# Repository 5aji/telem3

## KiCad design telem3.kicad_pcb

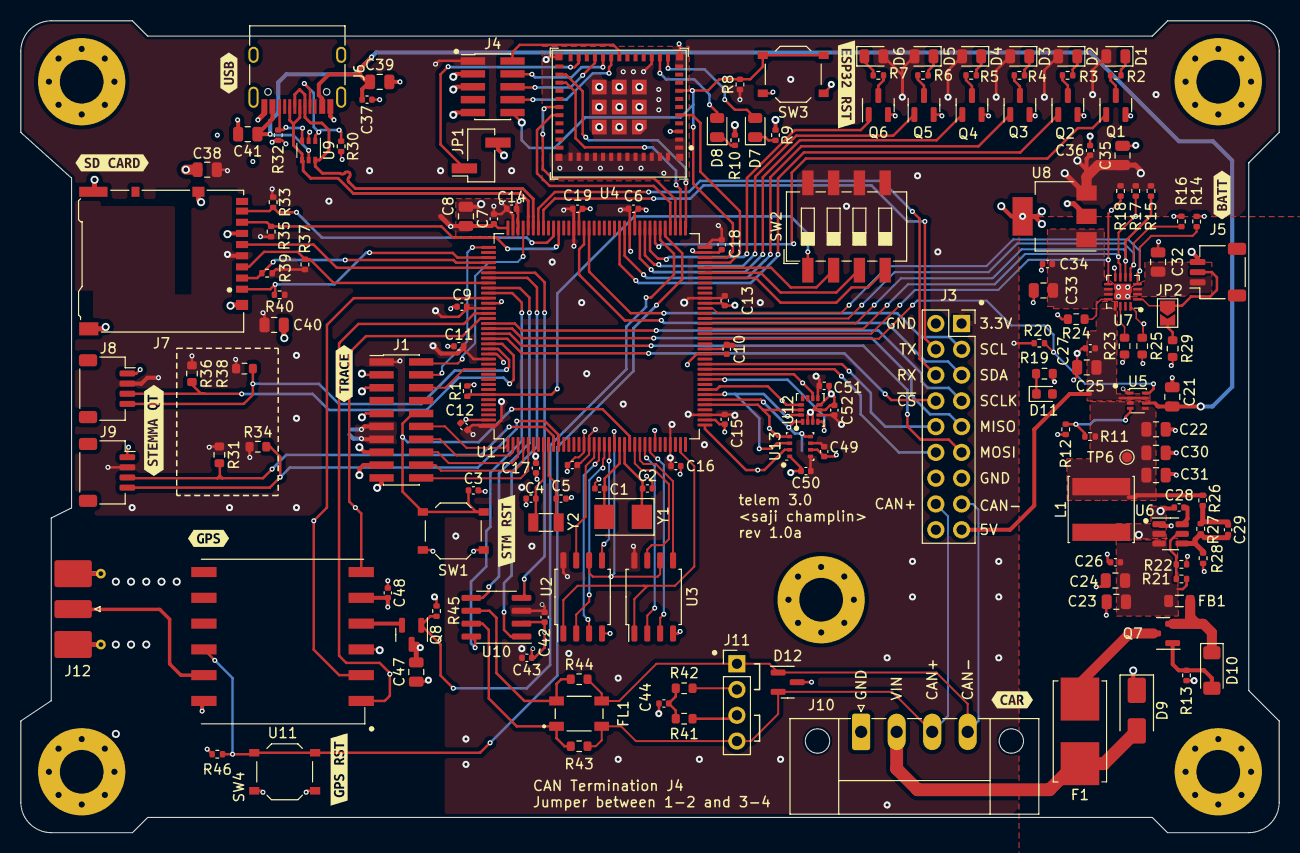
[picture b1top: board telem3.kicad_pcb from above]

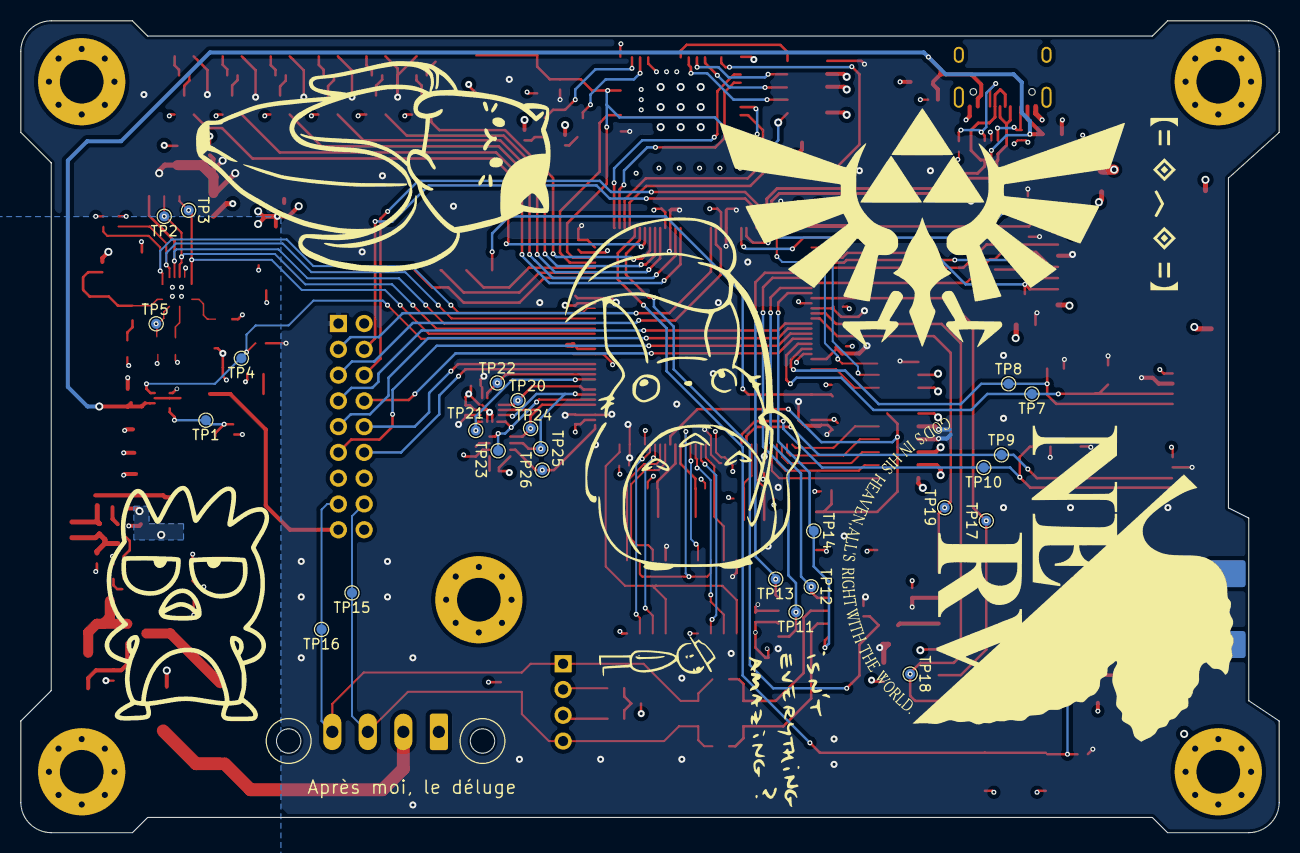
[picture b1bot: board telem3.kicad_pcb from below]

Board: 4 copper layers, 124.0 x 80.0 mm, 188 parts (25 on the bottom side), 139 nets.

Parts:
C1, C2: 20p; C_0402_1005Metric
C3, C9, C10, C11, C12, C13, C14, C15, C16, C17, C18, C19, C20, C26, C28, C34, C36, C37, C42, C43, C48, C49, C50, C51, C52: 0.1u; C_0402_1005Metric
C4, C5: 10p; C_0402_1005Metric
C6, C7, C27: 1u; C_0402_1005Metric
C8, C21, C22, C25, C32, C33, C35, C47: 4.7u; C_0805_2012Metric
C23, C24, C39, C41: 10u; C_0805_2012Metric
C29: 75p; C_0402_1005Metric
C30, C31, C38, C40: 22u; C_0805_2012Metric
C44: 4.7n; C_0402_1005Metric
D1: STA0; LED_0805_2012Metric
D2: STA1; LED_0805_2012Metric
D3: GOOD_LED; LED_0805_2012Metric
D4: STA2; LED_0805_2012Metric
D5: FAULT_LED; LED_0805_2012Metric
D6: STA3; LED_0805_2012Metric
D7: ESP_LED0; LED_0805_2012Metric
D8: ESP_LED1; LED_0805_2012Metric
D9: SMAJ30CA; D_SMA
D10: BZV55B10; D_MiniMELF
D11: 5V; LED_0603_1608Metric
D12: NUP2105L; SOT-23
F1: 2.5A; Fuseholder_Littelfuse_Nano2_154x
FB1: 600 @ 600MHz; L_0805_2012Metric
FL1: DLW43SH510XK2L; FIL_DLW43SH510XK2L
J1: STM32_TRACE; PinHeader_2x10_P1.27mm_Vertical_SMD
J3: EXPANSION_1; PinSocket_2x09_P2.54mm_Vertical
J4: ESP32_JTAG; PinHeader_2x05_P1.27mm_Vertical_SMD
J5: BAT; JST_SH_SM03B-SRSS-TB_1x03-1MP_P1.00mm_Horizontal
J6: STM_USBC; USB_C_Receptacle_HRO_TYPE-C-31-M-12
J7: Micro_SD_Card; microSD_HC_Hirose_DM3AT-SF-PEJM5
J8: QT1; JST_SH_SM04B-SRSS-TB_1x04-1MP_P1.00mm_Horizontal
J9: QT2; JST_SH_SM04B-SRSS-TB_1x04-1MP_P1.00mm_Horizontal
J10: Conn_01x04_Socket; PhoenixContact_MC_1,5_4-GF-3.5_1x04_P3.50mm_Horizontal_Thre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
J11: CAN_TERMINATION; PinHeader_1x04_P2.54mm_Vertical
J12: GPS_ANT; SMA_Molex_73251-2120_EdgeMount_Horizontal
JP1: ESP32_BOOTSEL; PinHeader_1x02_P2.54mm_Vertical_SMD_Pin1Right
JP2: BAT_TS_BYP; SolderJumper-2_P1.3mm_Open_TrianglePad1.0x1.5mm
L1: 15u; L_Changjiang_FNR6020S
Q1, Q2, Q3, Q4, Q5, Q6, Q8: 2N7002; SOT-23
Q7: IRLML9301; SOT-23
R1, R8, R11, R12, R13, R14, R15, R16, R17, R18, R20, R27, R33, R35, R37, R39, R40, R45, R46: 100k; R_0402_1005Metric
R2, R3, R4, R5, R6, R7, R9, R10: 330; R_0402_1005Metric
R19: 330; R_0603_1608Metric
R21: 511k; R_0402_1005Metric
R22: 105k; R_0402_1005Metric
R23: 46.4k; R_0603_1608Metric
R24: 1.18k; R_0603_1608Metric
R25: 1.13k; R_0603_1608Metric
R26: 49.9; R_0402_1005Metric
R28: 13.3k; R_0402_1005Metric
R29, R31, R34, R36, R38: 10k; R_0603_1608Metric
R30, R32: 5.1k; R_0402_1005Metric
R41, R42: 60R; R_0603_1608Metric
R43, R44: 0R; R_0603_1608Metric
SW1: RESET; SW_Push_1P1T_XKB_TS-1187A
SW2: OPT; SW_DIP_SPSTx04_Slide_6.7x11.72mm_W8.61mm_P2.54mm_LowProfile
SW3: ESP32_RST; SW_Push_1P1T_XKB_TS-1187A
SW4: GPS_RST; SW_Push_1P1T_XKB_TS-1187A
TP1: PR1; TestPoint_Pad_D1.0mm
TP2: ~{PGOOD}; TestPoint_Pad_D1.0mm
TP3: ~{CHG}; TestPoint_Pad_D1.0mm
TP4: ST; TestPoint_Pad_D1.0mm
TP5: BAT_CUR; TestPoint_Pad_D1.0mm
TP6: SW_5V; TestPoint_Pad_D1.0mm
TP7: QT1_SDA; TestPoint_Pad_D1.0mm
TP8: QT1_SCL; TestPoint_Pad_D1.0mm
TP9: QT2_SDA; TestPoint_Pad_D1.0mm
TP10: QT2_SCL; TestPoint_Pad_D1.0mm
TP11: CAN_TX; TestPoint_Pad_D1.0mm
TP12: CAN_SHDN; TestPoint_Pad_D1.0mm
TP13: CAN_RX; TestPoint_Pad_D1.0mm
TP14: CAN_STB; TestPoint_Pad_D1.0mm
TP15: CANH; TestPoint_Pad_D1.0mm
TP16: CANL; TestPoint_Pad_D1.0mm
TP17: GPS.TX; TestPoint_Pad_D1.0mm
TP18: GPS.RX; TestPoint_Pad_D1.0mm
TP19: 1PPS; TestPoint_Pad_D1.0mm
TP20: IMU_~{CS}; TestPoint_Pad_D1.0mm
TP21: IMU_INT_{1}; TestPoint_Pad_D1.0mm
TP22: IMU_INT_{2}; TestPoint_Pad_D1.0mm
TP23: SENSE_MISO; TestPoint_Pad_D1.0mm
TP24: SENSE_SCLK; TestPoint_Pad_D1.0mm
TP25: SENSE_MOSI; TestPoint_Pad_D1.0mm
TP26: BME_~{CS}; TestPoint_Pad_D1.0mm
U1: STM32L562ZETx; LQFP-144_20x20mm_P0.5mm
U2, U3: W25Q128JVS; SOIC-8_5.23x5.23mm_P1.27mm
U4: ESP32-C3-MINI-1; ESP32-C3-MINI-1U
U5: TPS2116; SOT-583-8
U6: TPS54202DDC; SOT-23-6
U7: BQ24075RGT; VQFN-16-1EP_3x3mm_P0.5mm_EP1.6x1.6mm
U8: AP7361C-33E; SOT-223-3_TabPin2
U9: NUP4202; SOT-363_SC-70-6
U10: TCAN334G; SOIC-8_3.9x4.9mm_P1.27mm
U11: L80-R; Quectel_L80-R
U12: LSM6DS3; LGA-14_3x2.5mm_P0.5mm_LayoutBorder3x4y
U13: BME280; Bosch_LGA-8_2.5x2.5mm_P0.65mm_ClockwisePinNumbering
Y1: 8MHz; Crystal_SMD_5032-2Pin_5.0x3.2mm
Y2: 32.768kHz; Crystal_SMD_3215-2Pin_3.2x1.5mm
kibuzzard-64E6B9AE: G***; kibuzzard-64E6B9AE
kibuzzard-64E6B9B9: G***; kibuzzard-64E6B9B9
kibuzzard-64E6B9C4: G***; kibuzzard-64E6B9C4
kibuzzard-64E6B9D9: G***; kibuzzard-64E6B9D9
kibuzzard-64E84E3F: G***; kibuzzard-64E84E3F
kibuzzard-64E84E26: G***; kibuzzard-64E84E26
kibuzzard-64EA17F0: G***; kibuzzard-64EA17F0
kibuzzard-64EA1880: G***; kibuzzard-64EA1880
kibuzzard-64ED289C: G***; kibuzzard-64ED289C
kibuzzard-64ED2075: G***; kibuzzard-64ED2075

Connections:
+3V3: C6.2, C7.2, C8.2, C9.2, C10.2, C11.2, C12.2, C13.2, C14.2, C15.2, C16.2, C17.2, C18.2, C19.2, C20.2, C35.1, C36.1, C38.1, C40.1, C42.1, C43.1, C47.2, C48.2, C49.1, C50.1, C51.1, C52.1, D1.2 (A), D2.2 (A), D3.2 (A), D4.2 (A), D5.2 (A), D6.2 (A), J1.1 (VTref), J1.11 (VTpwr), J1.13 (VTpwr), J3.1, J4.1 (VTref), J7.4 (VDD), J8.2, J9.2, Q8.3 (D), R8.1, R15.2, R17.2, R18.1, R20.1, R31.1, R33.1, R34.1, R35.1, R36.1, R37.1, R38.1, R39.1, R40.1, R45.1, R46.1, SW2.5, SW2.6, SW2.7, SW2.8, U1.6 (VBAT), U1.17 (VDD), U1.33 (VDDA), U1.39 (VDD), U1.52 (VDD), U1.62 (VDD), U1.72 (VDD), U1.84 (VDD), U1.95 (VDDIO2), U1.106 (VDDUSB), U1.108 (VDD), U1.121 (VDD), U1.131 (VDDIO2), U1.144 (VDD), U2.8 (VCC), U3.8 (VCC), U4.3 (3V3), U8.3 (VO), U10.3 (VCC), U11.5 (V_BCKP), U12.5 (VDDIO), U12.8 (VDD), U13.6 (VDDIO), U13.8 (VDD)
+5V: C25.1, C27.1, D11.2 (A), J3.17, U5.2 (VOUT), U5.7 (VOUT), U7.13 (IN)
/Board IO/CAN.RX: TP13.1, U1.114 (PD0), U10.4 (RXD)
/Board IO/CAN.SHDN: TP12.1, U1.117 (PD3), U10.5 (SHDN)
/Board IO/CAN.STB: TP14.1, U1.118 (PD4), U10.8 (STB)
/Board IO/CAN.TX: TP11.1, U1.115 (PD1), U10.1 (TXD)
/Board IO/QT1.SCL: J8.4, R38.2, TP8.1, U1.129 (PG14)
/Board IO/QT1.SDA: J8.3, R36.2, TP7.1, U1.128 (PG13)
/Board IO/QT2.SCL: J9.4, R34.2, TP10.1, U1.11 (PF1)
/Board IO/QT2.SDA: J9.3, R31.2, TP9.1, U1.10 (PF0)
/Board IO/SD.CLK: J7.5 (CLK), U1.113 (PC12)
/Board IO/SD.CMD: J7.3 (CMD), R37.2, U1.116 (PD2)
/Board IO/SD.DAT0: J7.7 (DAT0), R35.2, U1.98 (PC8)
/Board IO/SD.DAT1: J7.8 (DAT1), R33.2, U1.99 (PC9)
/Board IO/SD.DAT2: J7.1 (DAT2), R40.2, U1.111 (PC10)
/Board IO/SD.DAT3: J7.2 (DAT3/CD), R39.2, U1.112 (PC11)
/Board IO/USB_CC1: J6.A5 (CC1), R30.1, U9.1
/Board IO/USB_CC2: J6.B5 (CC2), R32.1, U9.3
/Board IO/USB_D+: J6.A6 (D+), J6.B6 (D+), U1.104 (PA12), U9.4
/Board IO/USB_D-: J6.A7 (D-), J6.B7 (D-), U1.103 (PA11), U9.6
/ESP32 Coprocessor/ESP32.CS: U1.73 (PB12), U4.26 (GPIO18/USB_D-)
/ESP32 Coprocessor/ESP32.EN: J4.10 (~RESET), R8.2, SW3.2, U1.70 (PB11), U4.8 (EN/CHIP_PU)
/ESP32 Coprocessor/ESP32.HNDSHK: U1.69 (PB10), U4.5 (GPIO2/ADC1_CH2)
/ESP32 Coprocessor/ESP32.MISO: U1.75 (PB14), U4.30 (GPIO20/U0RXD)
/ESP32 Coprocessor/ESP32.MOSI: U1.76 (PB15), U4.31 (GPIO21/U0TXD)
/ESP32 Coprocessor/ESP32.SCLK: U1.74 (PB13), U4.27 (GPIO19/USB_D+)
/ESP32 Coprocessor/LED0: D7.2 (A), U4.12 (GPIO0/ADC1_CH0/XTAL_32K_P)
/ESP32 Coprocessor/LED1: D8.2 (A), U4.13 (GPIO1/ADC1_CH1/XTAL_32K_N)
/ESP32 Coprocessor/TCLK: J4.4 (SWDCLK/TCK), U4.20 (GPIO6)
/ESP32 Coprocessor/TDI: J4.8 (NC/TDI), U4.19 (GPIO5/ADC2_CH0)
/ESP32 Coprocessor/TDO: J4.6 (SWO/TDO), U4.21 (GPIO7)
/ESP32 Coprocessor/TMS: J4.2 (SWDIO/TMS), U4.18 (GPIO4/ADC1_CH4)
/ESP32 Coprocessor/~DOWNLOAD: JP1.1 (A), U4.23 (GPIO9)
/MCU/BOOT0: R1.1, SW2.1, U1.138 (PH3)
/MCU/DEBUG_SWCLK: J1.4 (SWDCLK/TCK), U1.109 (PA14)
/MCU/DEBUG_SWDIO: J1.2 (SWDIO/TMS), U1.105 (PA13)
/MCU/DEBUG_SWO: J1.6 (SWO/TDO), U1.133 (PB3)
/MCU/DEBUG_TRACECLK: J1.12 (TRACECLK), U1.1 (PE2)
/MCU/DEBUG_TRACED0: J1.14 (TRACED0), U1.2 (PE3)
/MCU/DEBUG_TRACED1: J1.16 (TRACED1), U1.3 (PE4)
/MCU/DEBUG_TRACED2: J1.18 (TRACED2), U1.4 (PE5)
/MCU/DEBUG_TRACED3: J1.20 (TRACED3), U1.5 (PE6)
/MCU/EN1: R15.1, U1.57 (PG1), U7.6 (EN1)
/MCU/EN2: R16.2, U1.58 (PE7), U7.5 (EN2)
/MCU/FAULT_IND: Q5.1 (G), U1.81 (PD12)
/MCU/GOOD_IND: Q3.1 (G), U1.85 (PD14)
/MCU/GPS.1PPS: TP19.1, U1.123 (PD7), U11.6 (1PPS)
/MCU/GPS.RX: TP18.1, U1.122 (PD6), U11.1 (RXD1)
/MCU/GPS.TX: TP17.1, U1.119 (PD5), U11.2 (TXD1)
/MCU/GPS.~RST: R46.2, SW4.1, U1.77 (PD8), U11.10 (~RESET)
/MCU/HSE_IN: C1.2, U1.23 (PH0), Y1.2
/MCU/HSE_OUT: C2.2, U1.24 (PH1), Y1.1
/MCU/I2C3_SCL: J3.3, U1.92 (PG7)
/MCU/I2C3_SDA: J3.5, U1.93 (PG8)
/MCU/NRST: C3.1, J1.10 (~RESET), SW1.2, U1.25 (NRST)
/MCU/OCTOSPI_CLK: U1.22 (PF10), U2.6 (CLK), U3.6 (CLK)
/MCU/OCTOSPI_IO0: U1.20 (PF8), U2.2 (DO(IO1))
/MCU/OCTOSPI_IO1: U1.21 (PF9), U2.5 (DI(IO0))
/MCU/OCTOSPI_IO2: U1.19 (PF7), U2.3 (IO2)
/MCU/OCTOSPI_IO3: U1.18 (PF6), U2.7 (IO3)
/MCU/OCTOSPI_IO4: U1.27 (PC1), U3.5 (DI(IO0))
/MCU/OCTOSPI_IO5: U1.28 (PC2), U3.2 (DO(IO1))
/MCU/OCTOSPI_IO6: U1.29 (PC3), U3.3 (IO2)
/MCU/OCTOSPI_IO7: U1.26 (PC0), U3.7 (IO3)
/MCU/OCTOSPI_NCS: U1.35 (PA1), U2.1 (~CS), U3.1 (~CS)
/MCU/OPT0: SW2.2, U1.68 (PE15)
/MCU/OPT1: SW2.3, U1.67 (PE14)
/MCU/OPT2: SW2.4, U1.66 (PE13)
/MCU/PB2: J3.12, U1.48 (PB2)
/MCU/PD9: Q8.1 (G), R45.2, U1.78 (PD9)
/MCU/PF11: J3.10, U1.49 (PF11)
/MCU/RCC_OSC32_IN: C4.2, U1.8 (PC14), Y2.2
/MCU/RCC_OSC32_OUT: C5.2, U1.9 (PC15), Y2.1
/MCU/SENSE.BME_CS: TP26.1, U1.37 (PA3), U13.2 (CSB)
/MCU/SENSE.IMU_CS: TP20.1, U1.44 (PC4), U12.12 (CS)
/MCU/SENSE.IMU_INT1: TP21.1, U1.46 (PB0), U12.4 (INT1)
/MCU/SENSE.IMU_INT2: TP22.1, U1.47 (PB1), U12.9 (INT2)
/MCU/SENSE.MISO: TP23.1, U1.42 (PA6), U12.1 (SDO/SA0), U13.5 (SDO)
/MCU/SENSE.MOSI: TP25.1, U1.43 (PA7), U12.14 (SDA), U13.3 (SDI)
/MCU/SENSE.SCLK: TP24.1, U1.41 (PA5), U12.13 (SCL), U13.4 (SCK)
/MCU/SPI3_MISO: J3.9, U1.125 (PG10)
/MCU/SPI3_MOSI: J3.11, U1.126 (PG11)
/MCU/SPI3_NSS: J3.8, U1.127 (PG12)
/MCU/SPI3_SCK: J3.7, U1.124 (PG9)
/MCU/ST: R20.2, TP4.1, U1.54 (PF14), U5.8 (ST)
/MCU/STATUS_LED0: Q1.1 (G), U1.79 (PD10)
/MCU/STATUS_LED1: Q2.1 (G), U1.86 (PD15)
/MCU/STATUS_LED2: Q4.1 (G), U1.82 (PD13)
/MCU/STATUS_LED3: Q6.1 (G), U1.80 (PD11)
/MCU/USART1_RX: J3.6, U1.102 (PA10)
/MCU/USART1_TX: J3.4, U1.101 (PA9)
/MCU/~CE: R14.2, U1.60 (PE9), U7.4 (~CE)
/MCU/~CHG: R18.2, TP3.1, U1.55 (PF15), U7.9 (~CHG)
/MCU/~PGOOD: R17.1, TP2.1, U1.56 (PG0), U7.7 (~PGOOD)
/Power Management/BATP: C32.1, J5.1, U7.2 (BAT), U7.3 (BAT)
/Power Management/PR1: R11.2, R12.1, TP1.1, U5.4 (PR1)
/Power Management/RP_GATE: D10.2 (A), Q7.1 (G), R13.1
/Power Management/SW_5V: C22.1, C30.1, C31.1, L1.2, R11.1, R26.1, TP6.1, U5.3 (VIN1), U5.5 (MODE)
/Power Management/TS: J5.2, JP2.1 (A), U7.1 (TS)
/Power Management/V_{supp}: C33.1, C34.1, U7.10 (OUT), U7.11 (OUT), U8.1 (VI)
CAN+: D12.2 (K), FL1.2, J3.16, J10.3, J11.4, R43.2, TP15.1
CAN-: D12.1 (K), FL1.3, J3.15, J10.4, J11.1, R44.2, TP16.1
GND: C1.1, C2.1, C3.2, C4.1, C5.1, C6.1, C7.1, C8.1, C9.1, C10.1, C11.1, C12.1, C13.1, C14.1, C15.1, C16.1, C17.1, C18.1, C19.1, C20.1, C21.2, C22.2, C23.2, C24.2, C25.2, C26.2, C27.2, C30.2, C31.2, C32.2, C33.2, C34.2, C35.2, C36.2, C37.2, C38.2, C39.2, C40.2, C41.2, C42.2, C43.2, C44.2, C47.1, C48.1, C49.2, C50.2, C51.2, C52.2, D9.1 (A1), D12.3 (A), J1.3 (GND), J1.5 (GND), J1.9 (GNDDetect), J1.15 (GND), J1.17 (GND), J1.19 (GND), J3.2, J3.13, J4.3 (GND), J4.5 (GND), J4.9 (GNDDetect), J5.3, J6.A1 (GND), J6.A12 (GND), J6.B1 (GND), J6.B12 (GND), J6.S1 (SHIELD), J7.6 (VSS), J7.11 (SHIELD), J8.1, J9.1, J10.1, J12.2 (Ext), JP1.2 (B), Q1.2 (S), Q2.2 (S), Q3.2 (S), Q4.2 (S), Q5.2 (S), Q6.2 (S), R1.2, R9.1, R10.1, R12.2, R13.2, R14.1, R16.1, R19.2, R22.2, R23.1, R24.1, R25.2, R28.2, R29.2, R30.2, R32.2, SW1.1, SW3.1, SW4.2, U1.16 (VSS), U1.30 (VSSA), U1.38 (VSS), U1.51 (VSS), U1.61 (VSS), U1.71 (VSS), U1.83 (VSS), U1.94 (VSS), U1.107 (VSS), U1.120 (VSS), U1.130 (VSS), U1.143 (VSS), U2.4 (GND), U3.4 (GND), U4.1 (GND), U4.2 (GND), U4.11 (GND), U4.14 (GND), U4.36 (GND), U4.37 (GND), U4.38 (GND), U4.39 (GND), U4.40 (GND), U4.41 (GND), U4.42 (GND), U4.43 (GND), U4.44 (GND), U4.45 (GND), U4.46 (GND), U4.47 (GND), U4.48 (GND), U4.49 (GND), U4.50 (GND), U4.51 (GND), U4.52 (GND), U4.53 (GND), U5.1 (GND), U6.1 (GND), U7.8 (VSS), U7.17 (VSS), U8.2 (GND), U9.2, U10.2 (GND), U11.3 (GND), U11.12 (GND), U12.2 (SDX), U12.3 (SCX), U12.6 (GND), U12.7 (GND), U13.1 (GND), U13.7 (GND)
unnamed: C29.1, R26.2, R27.1
unnamed: C44.1, R41.1, R42.2
unnamed: D1.1 (K), R2.1
unnamed: D2.1 (K), R3.1
unnamed: D3.1 (K), R4.1
unnamed: D4.1 (K), R5.1
unnamed: D5.1 (K), R6.1
unnamed: D6.1 (K), R7.1
unnamed: D7.1 (K), R9.2
unnamed: D8.1 (K), R10.2
unnamed: D10.1 (K), FB1.1, Q7.2 (S)
unnamed: D11.1 (K), R19.1
unnamed: J11.2, R42.1
unnamed: J11.3, R41.2
unnamed: J12.1 (In), U11.11 (RESERVED)
unnamed: JP2.2 (B), R29.1
unnamed: Q1.3 (D), R2.2
unnamed: Q2.3 (D), R3.2
unnamed: Q3.3 (D), R4.2
unnamed: Q4.3 (D), R5.2
unnamed: Q5.3 (D), R6.2
unnamed: Q6.3 (D), R7.2
unnamed: F1.2, Q7.3 (D)
unnamed: Q8.2 (S), U11.4 (VCC)
unnamed: C28.1, U6.6 (BOOT)
unnamed: R21.2, R22.1, U6.5 (EN)
unnamed: C29.2, R27.2, R28.1, U6.4 (FB)
unnamed: C28.2, L1.1, U6.2 (SW)
unnamed: C23.1, C24.1, C26.1, FB1.2, R21.1, U6.3 (VIN)
unnamed: R24.2, U7.12 (ILIM)
unnamed: R25.1, TP5.1, U7.16 (ISET)
unnamed: R23.2, U7.14 (TMR)
unnamed: FL1.1, R43.1, U10.7 (CANH)
unnamed: FL1.4, R44.1, U10.6 (CANL)
VBUS: C21.1, C37.1, C39.1, C41.1, J6.A4 (VBUS), J6.A9 (VBUS), J6.B4 (VBUS), J6.B9 (VBUS), U5.6 (VIN2), U9.5
VDC: D9.2 (A2), F1.1, J10.2

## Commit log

2023-08-29 rev 1.0a
2023-08-30 minor schematic reorg
2023-09-08 fix uart gps
2023-09-11 fix right board edge
2024-02-25 not quite sure
